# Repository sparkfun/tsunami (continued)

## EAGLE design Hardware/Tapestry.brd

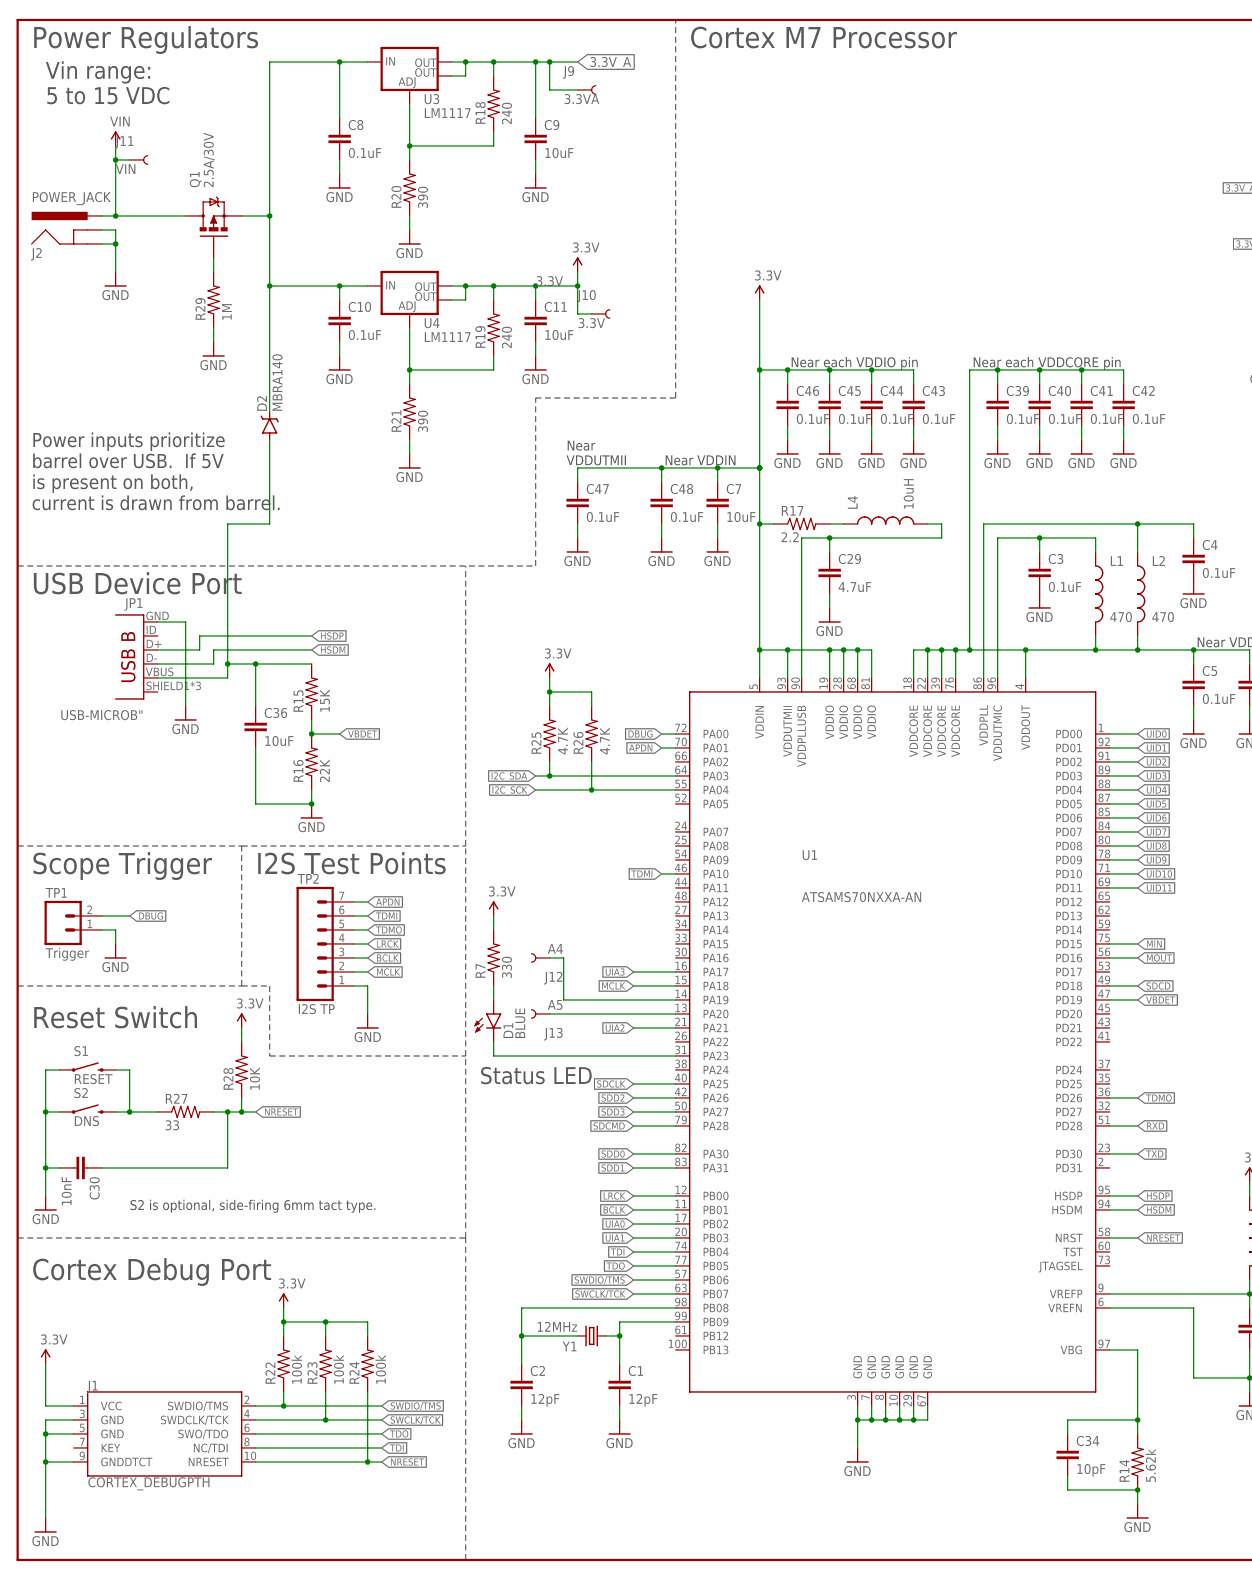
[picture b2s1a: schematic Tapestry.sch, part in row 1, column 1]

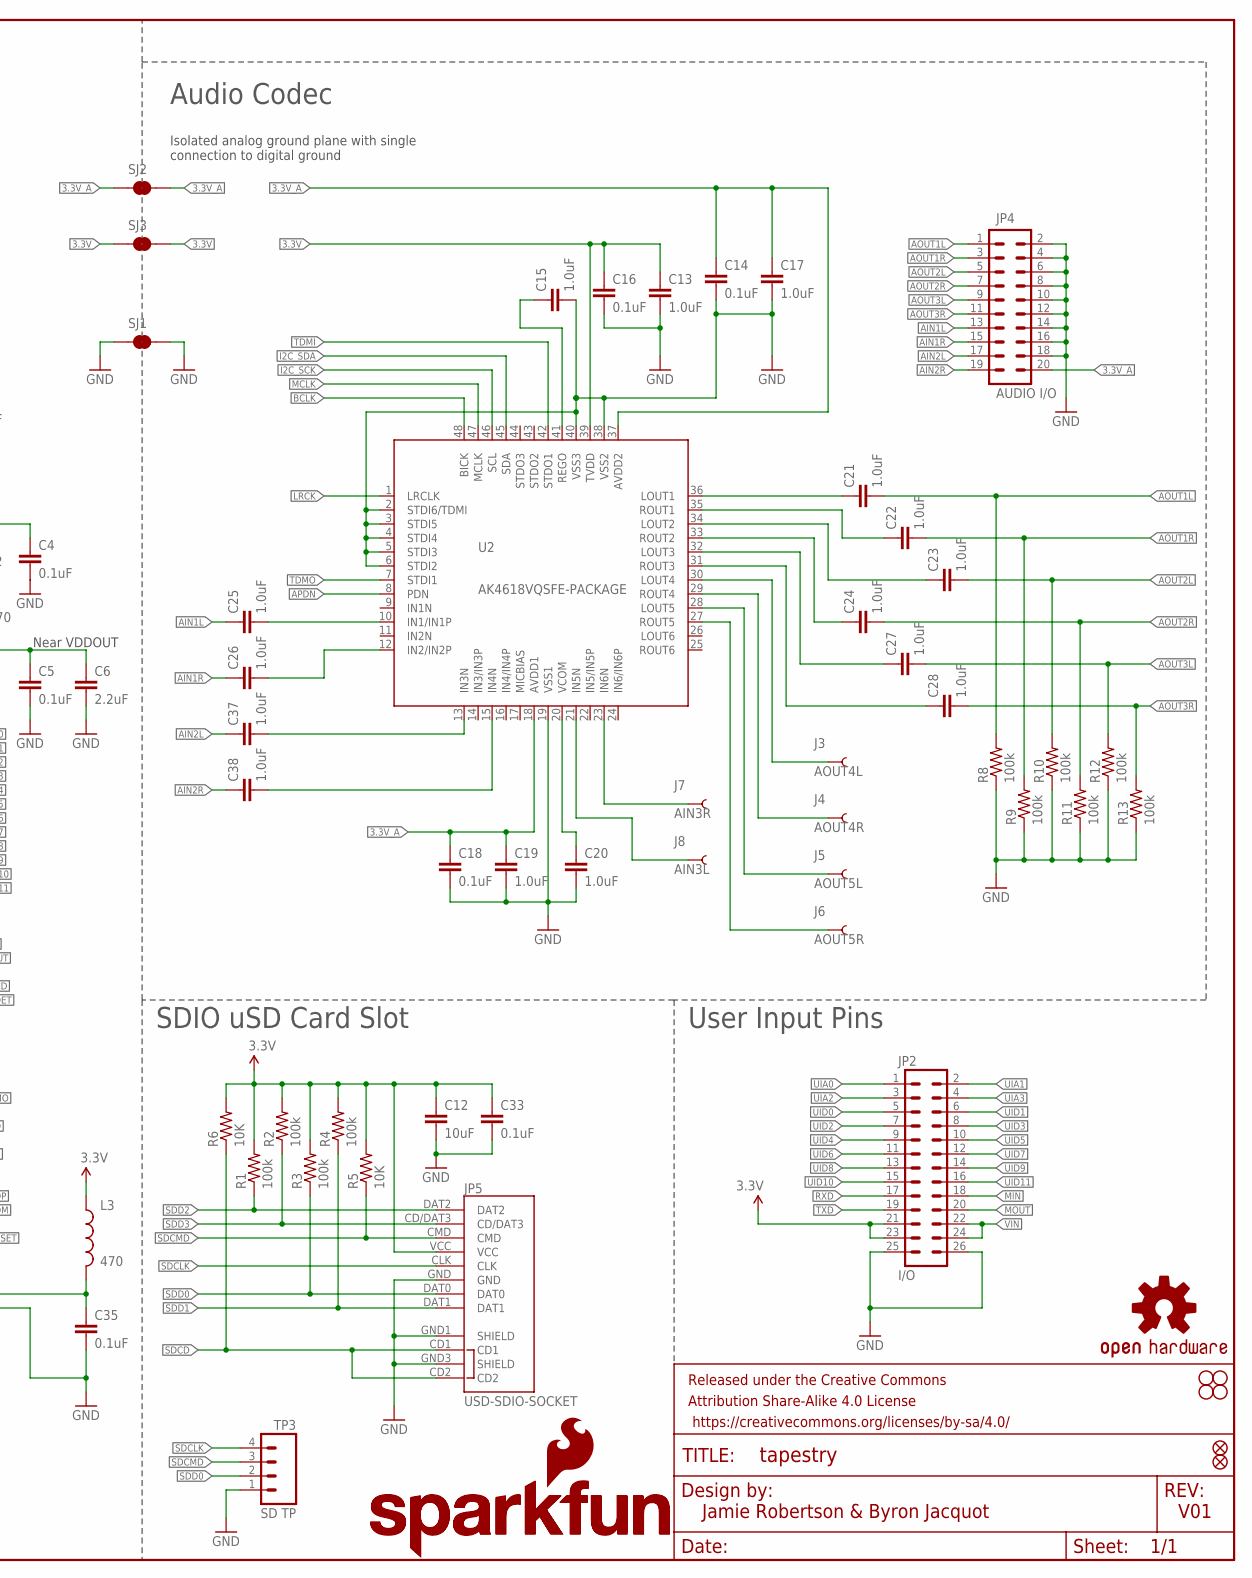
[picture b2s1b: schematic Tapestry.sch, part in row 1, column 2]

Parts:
C1, C2: 12pF; 0603-CAP
C3, C4, C5, C8, C10, C14, C16, C18, C33, C35, C39, C40, C41, C42, C43, C44, C45, C46, C47, C48: 0.1uF; 0603-CAP
C6: 2.2uF; 0603-CAP
C7, C9, C11, C12, C36: 10uF; 0603-CAP
C13, C15, C17, C19, C20, C21, C22, C23, C24, C25, C26, C27, C28, C37, C38: 1.0uF; 0603-CAP
C29: 4.7uF; 0603-CAP
C30: 10nF; 0603-CAP
C34: 10pF; 0603-CAP
D1: BLUE; LED-0603
D2: MBRA140; SMA-DIODE
FD1, FD2: FIDUCIALUFIDUCIAL; MICRO-FIDUCIAL
FRAME1: FRAME-LEDGER; CREATIVE_COMMONS
J1: CORTEX_DEBUGPTH; 2X5-PTH-1.27MM
J2: POWER_JACK; POWER_JACK_PTH_LOCK
J3: AOUT4L; TP_15TH
J4: AOUT4R; TP_15TH
J5: AOUT5L; TP_15TH
J6: AOUT5R; TP_15TH
J7: AIN3R; TP_15TH
J8: AIN3L; TP_15TH
J9: 3.3VA; TP_15TH
J10: 3.3V; TP_15TH
J11: VIN; TP_15TH
J12: A4; TP_15TH
J13: A5; TP_15TH
JP1: USB-MICROB"; USB-B-MICRO-SMD_V03
JP2: I/O; 2X13
JP4: AUDIO I/O; 2X10
JP5: USD-SDIO-SOCKET; MICRO-SD-SOCKET-SDIO
L1, L2, L3: 470; 0603
L4: 10uH; 0805
LOGO1: SFE_LOGO_NAME_FLAME.2_INCH; SFE_LOGO_NAME_FLAME_.2
LOGO2: OSHW-LOGOM; OSHW-LOGO-M
LOGO3: SFE_LOGO_NAME.2_INCH; SFE_LOGO_NAME_.2
Q1: 2.5A/30V; SOT23-3
R1, R2, R3, R4, R8, R9, R10, R11, R12, R13, R22, R23, R24: 100k; 0603-RES
R5, R6, R28: 10K; 0603-RES
R7: 330; 0603-RES
R14: 5.62k; 0603-RES
R15: 15K; 0603-RES
R16: 22K; 0603-RES
R17: 2.2; 0603-RES
R18, R19: 240; 0603-RES
R20, R21: 390; 0603-RES
R25, R26: 4.7K; 0603-RES
R27: 33; 0603-RES
R29: 1M; 0603-RES
S1: RESET; TACTILE-SWITCH-SMD
S2: DNS; TACTILE-PTH-SIDEEZ
SJ1, SJ2, SJ3: JUMPER-PAD-2-NC_BY_TRACE; PAD-JUMPER-2-NC_BY_TRACE_YES_SILK
STANDOFF1, STANDOFF2, STANDOFF3, STANDOFF4: STAND-OFF
TP1: Trigger; 1X02_NO_SILK
TP2: I2S TP; 1X07_NO_SILK
TP3: SD TP; 1X04_NO_SILK
U1: ATSAMS70NXXA-AN; LQFP100
U2: AK4618VQSFE-PACKAGE; LQFP-48
U3, U4: LM1117; SOT223
Y1: 12MHz; CRYSTAL-SMD-5X3

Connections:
3.3V: C7.1, C11.1, C12.1, C13.1, C16.1, C33.1, C43.1, C44.1, C45.1, C46.1, C47.1, C48.1, J1.1 (VCC), J10.P$1, JP2.21, JP2.23, JP5.VCC, L3.1, R1.2, R2.2, R3.2, R4.2, R5.2, R6.2, R7.2, R17.1, R19.2, R22.2, R23.2, R24.2, R25.2, R26.2, R28.2, SJ3.1, SJ3.2, U1.5 (VDDIN), U1.19 (VDDIO), U1.28 (VDDIO), U1.68 (VDDIO), U1.81 (VDDIO), U1.93 (VDDUTMII), U2.39 (TVDD), U4.2 (OUT), U4.4 (OUT)
3.3V_A: C9.1, C14.1, C17.1, C18.1, C19.1, J9.P$1, JP4.20, R18.2, SJ2.1, SJ2.2, U2.18 (AVDD1), U2.37 (AVDD2), U3.2 (OUT), U3.4 (OUT)
AIN1L: C25.1, JP4.13
AIN1R: C26.1, JP4.15
AIN2L: C37.1, JP4.17
AIN2R: C38.1, JP4.19
AOUT1L: C21.2, JP4.1, R8.2
AOUT1R: C22.2, JP4.3, R9.2
AOUT2L: C23.2, JP4.5, R10.2
AOUT2R: C24.2, JP4.7, R11.2
AOUT3L: C27.2, JP4.9, R12.2
AOUT3R: C28.2, JP4.11, R13.2
APDN: TP2.7, U1.70 (PA01), U2.8 (PDN)
BCLK: TP2.3, U1.11 (PB01), U2.48 (BICK)
DBUG: TP1.2, U1.72 (PA00)
GND: C1.2, C2.2, C3.2, C4.2, C5.2, C6.2, C7.2, C8.2, C9.2, C10.2, C11.2, C12.2, C13.2, C14.2, C15.2, C16.2, C17.2, C18.2, C19.2, C20.2, C29.2, C30.2, C33.2, C34.2, C35.2, C36.2, C39.2, C40.2, C41.2, C42.2, C43.2, C44.2, C45.2, C46.2, C47.2, C48.2, J1.3 (GND), J1.5 (GND), J1.9 (GNDDTCT), J2.GND, J2.GNDBREAK, JP1.GND, JP2.25, JP2.26, JP4.2, JP4.4, JP4.6, JP4.8, JP4.10, JP4.12, JP4.14, JP4.16, JP4.18, JP5.GND, JP5.GND1 (SHIELD), JP5.GND3 (SHIELD), R8.1, R9.1, R10.1, R11.1, R12.1, R13.1, R14.1, R16.1, R20.1, R21.1, R29.1, S1.1, S2.1, SJ1.1, SJ1.2, TP1.1, TP2.1, TP3.1, U1.3 (GND), U1.6 (VREFN), U1.7 (GND), U1.8 (GND), U1.10 (GND), U1.29 (GND), U1.67 (GND), U2.2 (STDI6/TDMI), U2.3 (STDI5), U2.4 (STDI4), U2.5 (STDI3), U2.6 (STDI2), U2.19 (VSS1), U2.38 (VSS2), U2.40 (VSS3)
HSDM: JP1.D-, U1.94 (HSDM)
HSDP: JP1.D+, U1.95 (HSDP)
I2C_SCK: R26.1, U1.55 (PA04), U2.46 (SCL)
I2C_SDA: R25.1, U1.64 (PA03), U2.45 (SDA)
LRCK: TP2.4, U1.12 (PB00), U2.1 (LRCLK)
MCLK: TP2.2, U1.15 (PA18), U2.47 (MCLK)
MIN: JP2.18, U1.75 (PD15)
MOUT: JP2.20, U1.56 (PD16)
unnamed: C2.1, U1.98 (PB08), Y1.3 (2)
unnamed: C1.1, U1.99 (PB09), Y1.1
unnamed: C3.1, L1.1, U1.96 (VDDUTMIC)
unnamed: C29.1, L4.2, U1.90 (VDDPLLUSB)
unnamed: C4.1, L2.1, U1.86 (VDDPLL)
unnamed: C15.1, U2.41 (REGO)
unnamed: C36.1, D2.A, JP1.VBUS, R15.2
unnamed: C8.1, C10.1, D2.C, Q1.2 (S), U3.3 (IN), U4.3 (IN)
unnamed: D1.C, U1.31 (PA23)
unnamed: D1.A, R7.1
unnamed: C20.1, U2.20 (VCOM)
unnamed: C21.1, U2.36 (LOUT1)
unnamed: C26.2, U2.12 (IN2/IN2P)
unnamed: C25.2, U2.10 (IN1/IN1P)
unnamed: C34.1, R14.2, U1.97 (VBG)
unnamed: C35.1, L3.2, U1.9 (VREFP)
unnamed: C22.1, U2.35 (ROUT1)
unnamed: C23.1, U2.34 (LOUT2)
unnamed: C24.1, U2.33 (ROUT2)
unnamed: C27.1, U2.32 (LOUT3)
unnamed: C28.1, U2.31 (ROUT3)
unnamed: C37.2, U2.13 (IN3N)
unnamed: L4.1, R17.2
unnamed: R18.1, R20.2, U3.1 (ADJ)
unnamed: R27.1, S1.3 (2), S2.2
unnamed: C38.2, U2.15 (IN4N)
unnamed: J7.P$1, U2.23 (IN6N)
unnamed: R19.1, R21.2, U4.1 (ADJ)
unnamed: J8.P$1, U2.21 (IN5N)
unnamed: J3.P$1, U2.30 (LOUT4)
unnamed: J4.P$1, U2.29 (ROUT4)
unnamed: J5.P$1, U2.28 (LOUT5)
unnamed: J6.P$1, U2.27 (ROUT5)
unnamed: J12.P$1, U1.14 (PA19)
unnamed: J13.P$1, U1.13 (PA20)
unnamed: Q1.1 (G), R29.2
NRESET: C30.1, J1.10 (NRESET), R24.1, R27.2, R28.1, U1.58 (NRST)
RXD: JP2.17, U1.51 (PD28)
SDCD: JP5.CD1, JP5.CD2, R6.1, U1.49 (PD18)
SDCLK: JP5.CLK, TP3.4, U1.40 (PA25)
SDCMD: JP5.CMD, R5.1, TP3.3, U1.79 (PA28)
SDD0: JP5.DAT0, R3.1, TP3.2, U1.82 (PA30)
SDD1: JP5.DAT1, R4.1, U1.83 (PA31)
SDD2: JP5.DAT2, R1.1, U1.42 (PA26)
SDD3: JP5.CD/DAT3, R2.1, U1.50 (PA27)
SWCLK/TCK: J1.4 (SWDCLK/TCK), R23.1, U1.63 (PB07)
SWDIO/TMS: J1.2 (SWDIO/TMS), R22.1, U1.57 (PB06)
TDI: J1.8 (NC/TDI), U1.74 (PB04)
TDMI: TP2.6, U1.46 (PA10), U2.42 (STDO1)
TDMO: TP2.5, U1.36 (PD26), U2.7 (STDI1)
TDO: J1.6 (SWO/TDO), U1.77 (PB05)
TXD: JP2.19, U1.23 (PD30)
UIA0: JP2.1, U1.17 (PB02)
UIA1: JP2.2, U1.20 (PB03)
UIA2: JP2.3, U1.21 (PA21)
UIA3: JP2.4, U1.16 (PA17)
UID0: JP2.5, U1.1 (PD00)
UID1: JP2.6, U1.92 (PD01)
UID2: JP2.7, U1.91 (PD02)
UID3: JP2.8, U1.89 (PD03)
UID4: JP2.9, U1.88 (PD04)
UID5: JP2.10, U1.87 (PD05)
UID6: JP2.11, U1.85 (PD06)
UID7: JP2.12, U1.84 (PD07)
UID8: JP2.13, U1.80 (PD08)
UID9: JP2.14, U1.78 (PD09)
UID10: JP2.15, U1.71 (PD10)
UID11: JP2.16, U1.69 (PD11)
VBDET: R15.1, R16.2, U1.47 (PD19)
VDDOUT: C5.1, C6.1, C39.1, C40.1, C41.1, C42.1, L1.2, L2.2, U1.4 (VDDOUT), U1.18 (VDDCORE), U1.22 (VDDCORE), U1.39 (VDDCORE), U1.76 (VDDCORE)
VIN: J2.PWR, J11.P$1, JP2.22, JP2.24, Q1.3 (D)

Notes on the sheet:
Isolated analog ground plane with single connection to digital ground
Jamie Robertson & Byron Jacquot
V01
Near each VDDCORE pin
Near each VDDIO pin
Near VDDUTMII
Near VDDIN
Near VDDOUT
Power Regulators
USB Device Port
Scope Trigger
I2S Test Points
Cortex Debug Port
Cortex M7 Processor
Audio Codec
SDIO uSD Card Slot
User Input Pins
Reset Switch
S2 is optional, side-firing 6mm tact type.
Vin range: 5 to 15 VDC
Status LED
Power inputs prioritize barrel over USB. If 5V is present on both, current is drawn from barrel.

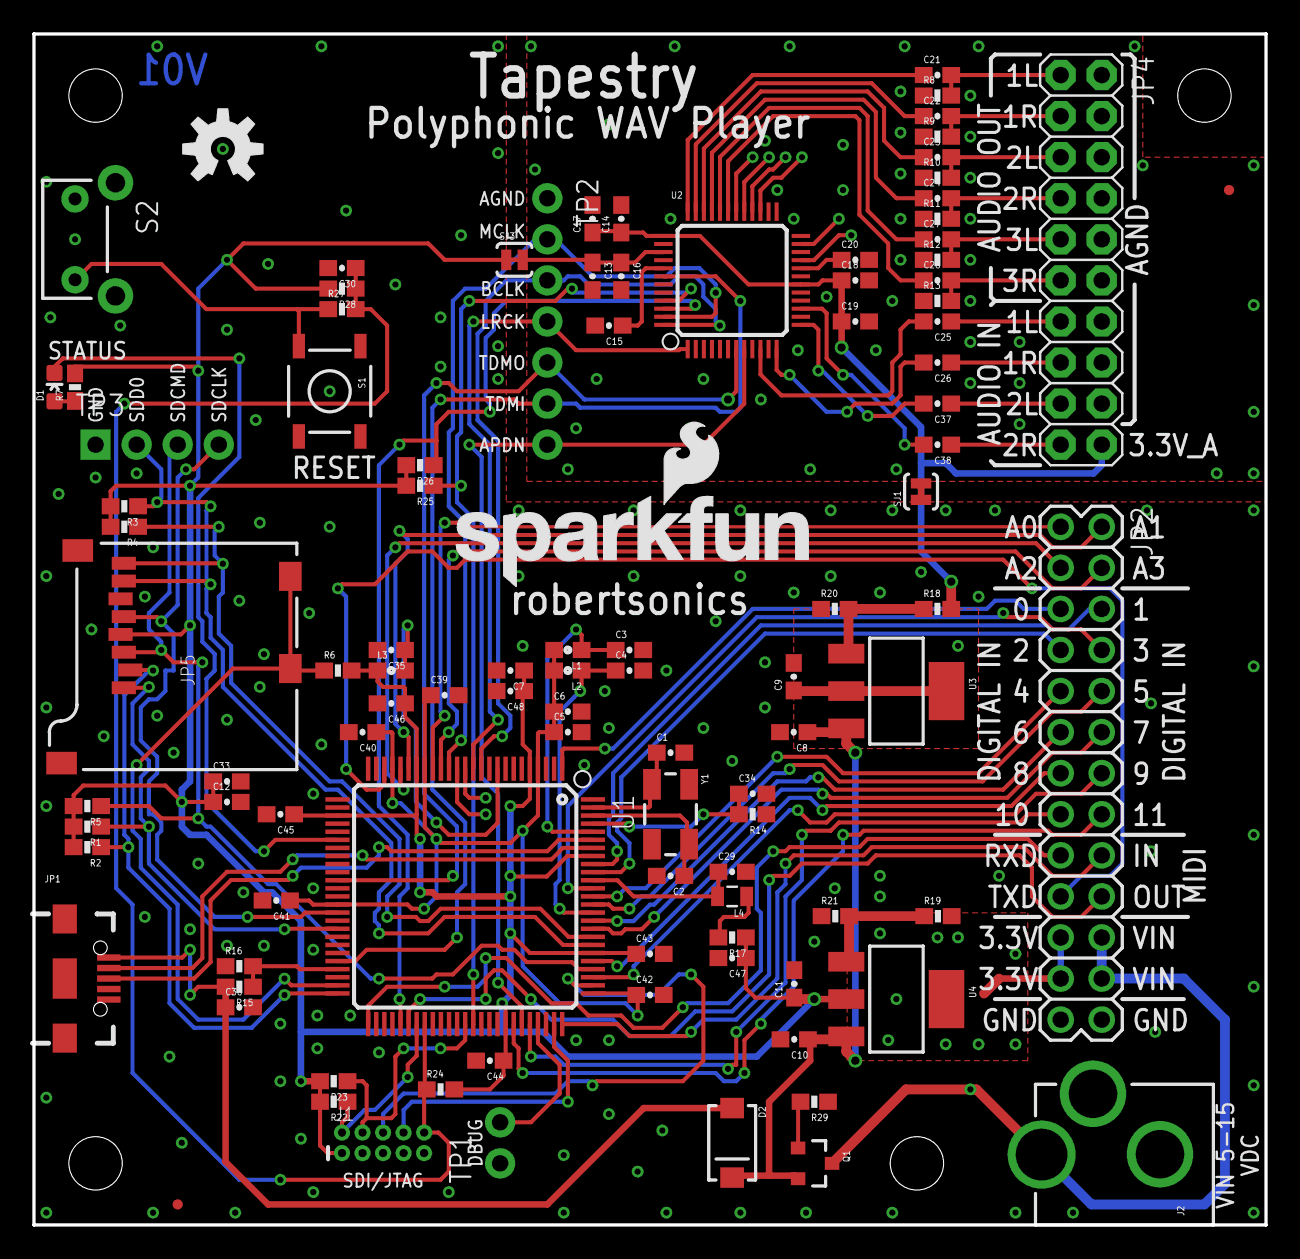
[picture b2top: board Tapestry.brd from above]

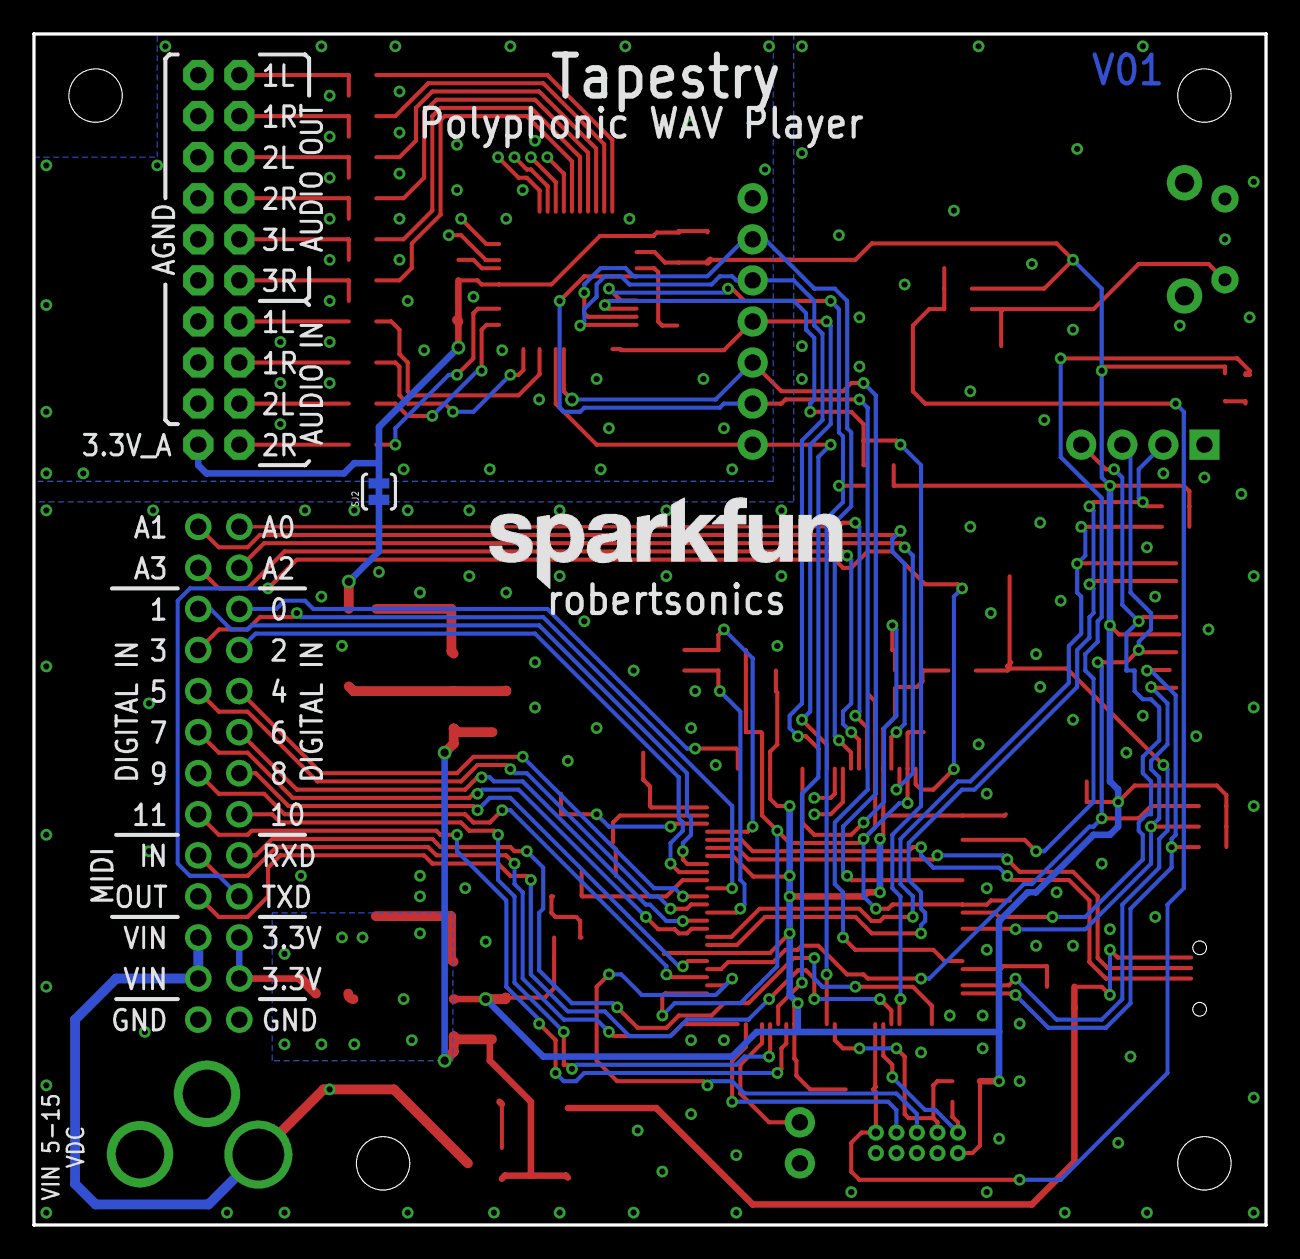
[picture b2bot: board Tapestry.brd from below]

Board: 2 copper layers, 76.2 x 73.7 mm, 122 parts (2 on the bottom side), 95 nets.
